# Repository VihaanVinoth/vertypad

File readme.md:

# VertyPad

The **VertyPad** is a custom 4x2 matrix mechanical macropad, featuring a rotary encoder, and a 0.91-inch OLED screen. It is built with the Seeed Studio XIAO RP2040 microcontroller, powered by QMK, and supports **cross-platform switching (macOS and Windows)** with an **interactive OLED UI menu**.

### PCB

### Schematics

### CAD

## BOM

| Component Type | Part Description | Quantity |
| :--- | :--- | :--- | 
| **Microcontroller** | Seeed Studio XIAO RP2040 | 1 |
| **Switches** | Cherry MX-Style Mechanical Switches | 7 |
| **Rotary Encoder** | EC11 Rotary Encoder with Switch | 1 | 
| **Diodes** | 1N4148 Through-Hole Signal Diodes | 8 |
| **Display Panel** | 0.91-inch I2C Monochromatic OLED | 1 | 
| **Keycaps** | DSA Profile Blank Keycaps | 7 | 
| **Screws**| M3 x 16mm Screws | 4 | 
| **Case** | 3D Printed Case/Plate | 1 |
| **PCB** | A PCB | 1 |

## Keymap & Feature Profiles

The VertyPad supports various macro commands across MacOS and Windows:

* **Copy:** `Command + C` (macOS) or `Control + C` (Windows).
* **Paste:** `Command + V` (macOS) or `Control + V` (Windows).
* **Spotlight/Search:** Launches Apple Spotlight Search (`Cmd + Space`) or Windows Search (`Win + S`).
* **Lock:** Locks the screen (`Cmd + Ctrl + Q` on Mac, `Win + L` on Windows).
* **Standard Keycodes:** Standard layout keycodes (`KC_4` and `KC_6`).
* **UI Select** Interactively toggles configuration states, such as switching between macOS and Windows modes on the OLED screen.
* **Rotary Dial Turn:** Cycles forward and backward through the **OLED UI menu screens** (Dashboard, OS Config, and Hardware Status).
* **Encoder Click Button (SW8):** Instant system audio stream mute toggle (`KC_MUTE`).

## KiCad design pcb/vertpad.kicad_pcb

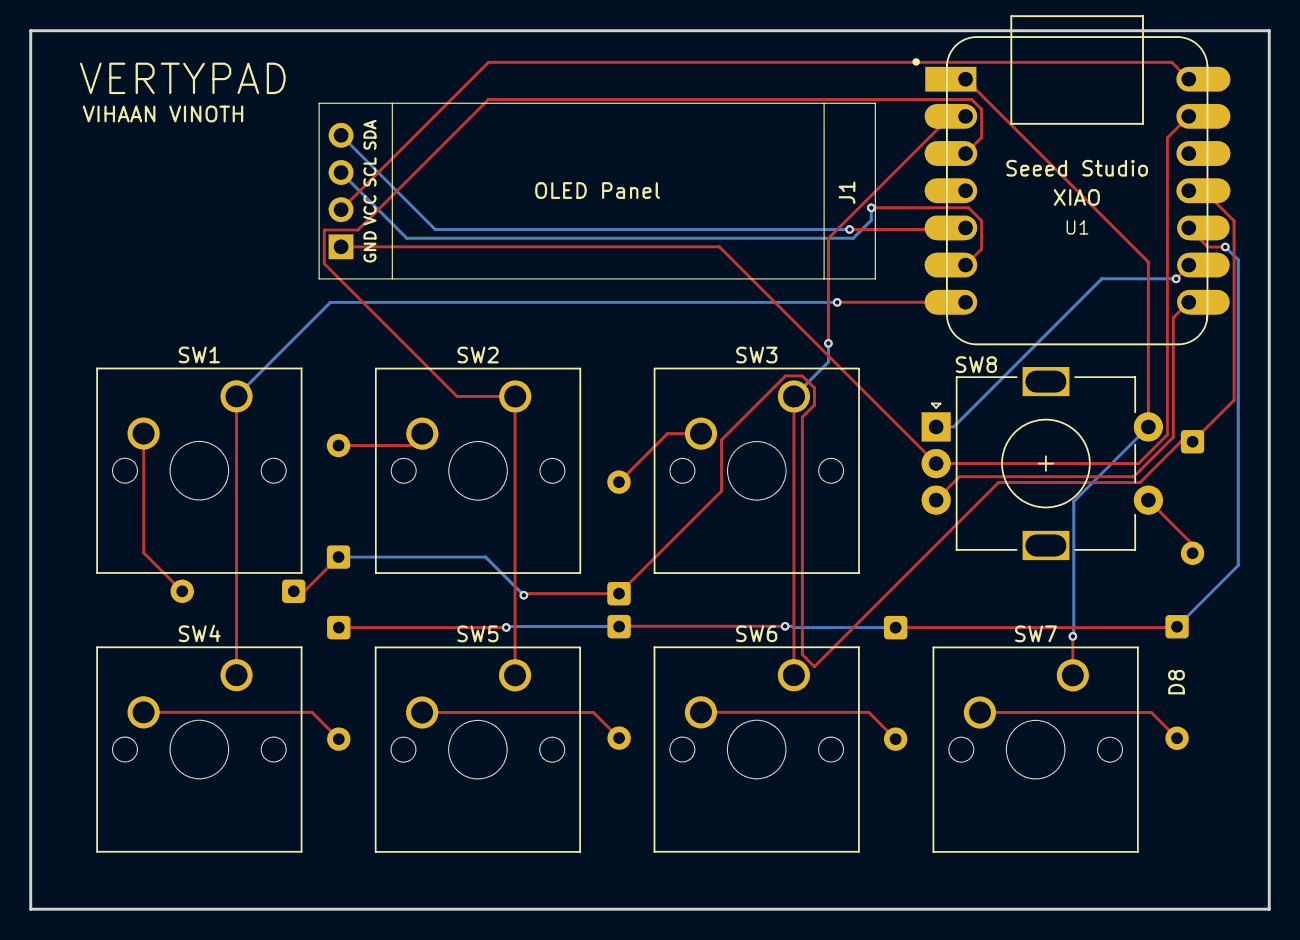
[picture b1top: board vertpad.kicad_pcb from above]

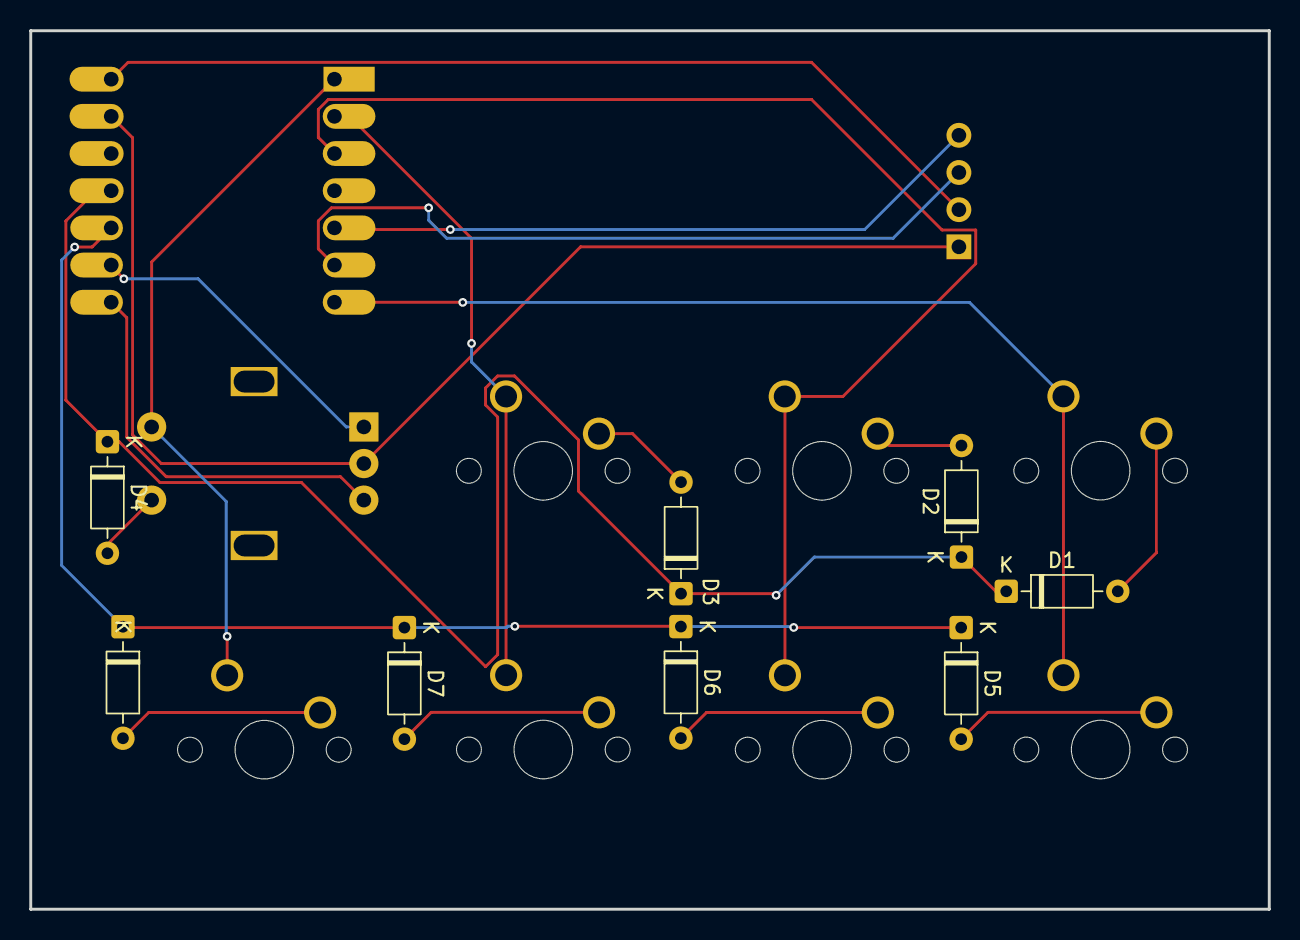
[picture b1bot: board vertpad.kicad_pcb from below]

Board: 2 copper layers, 84.6 x 60.0 mm, 18 parts (8 on the bottom side), 20 nets.

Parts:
D1, D2, D3, D4, D5, D6, D7, D8: D; D_DO-35_SOD27_P7.62mm_Horizontal
J1: OLED_DISPLAY; SSD1306-0.91-OLED-4pin-128x32
SW1, SW2, SW3, SW4, SW5, SW6, SW7: SW_Push_45deg; SW_Cherry_MX_1.00u_PCB
SW8: RotaryEncoder_Switch; RotaryEncoder_Alps_EC11E-Switch_Vertical_H20mm
U1: MOUDLE-SEEEDUINO-XIAO; XIAO-Generic-Hybrid-14P-2.54-21X17.8MM

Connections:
+5V: J1.2, U1.14 (5V)
COL0: SW1.1, SW4.1, U1.7 (PB08_A6_D6_TX)
COL1: SW2.1, SW5.1, U1.3 (PA10_A2_D2)
COL2: SW3.1, SW6.1, U1.2 (PA4_A1_D1)
COL3: SW7.1, SW8.S2, U1.1 (PA02_A0_D0)
GND: J1.1, SW8.C, U1.13 (GND)
unnamed: D1.2 (A), SW1.2
unnamed: D2.2 (A), SW2.2
unnamed: D3.2 (A), SW3.2
unnamed: D4.2 (A), SW8.S1
unnamed: D5.2 (A), SW4.2
unnamed: D6.2 (A), SW5.2
unnamed: D7.2 (A), SW6.2
unnamed: D8.2 (A), SW7.2
RNA: SW8.A, U1.9 (PA7_A8_D8_SCK)
RNB: SW8.B, U1.8 (PB09_A7_D7_RX)
ROW0: D1.1 (K), D2.1 (K), D3.1 (K), D4.1 (K), U1.11 (PA6_A10_D10_MOSI)
ROW1: D5.1 (K), D6.1 (K), D7.1 (K), D8.1 (K), U1.10 (PA5_A9_D9_MISO)
SCL: J1.3, U1.6 (PA9_A5_D5_SCL)
SDA: J1.4, U1.5 (PA8_A4_D4_SDA)
